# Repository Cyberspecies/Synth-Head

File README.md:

# Synth Head
To create an open source suit which can be worn by an individual and customised to their will. It also must be constructed in such a way that an average human could build it within a reasonable budget and time. The suit must be modular whilst remaining safe for the user to operate. The software must be easy to configure for any individual and has capability to modify without the need to always reflashing its firmware. The project was created according to this standard however, it has evolved over time to be more of a testing ground for sensors and other features of the like as I will continue this along with other projects I have due to compatibility.

## Overview
This project is always in the works and will be updated. Although regular updates are not possible due to me still being in uni, I will do what I can. This repo is basically a better version of the other repo and a true migration as the old one due to its structure. The reason for it being a new repo rather then just a fix is cause the title changed so the old link wouldn't have worked anyway. The current design is DX which stands for Design 10 as it is the 10th time the base shape has changed, the .3 at the end is an iterator for which version were on.

### Features
* <strong style='color: #99ccff;'>Vacuum Formed Visor</strong> allows the user to see out of a clear shell rather then the previous mesh version which caused chromatic abberation, preventing the true colours of the display from emiting through the visor properly.
* <strong style='color: #99ccff;'>Detachable Substructure</strong> which conformes to the visor ridge provides an easy to modify platform to which different displays, sensors and other modules.
* <strong style='color: #99ccff;'>Builtin Head Restraint</strong> was designed to hold in an average head with relatively high pressure, although the pressure seems like it cause pain, the addition of a foam pad mitigates this and is actually comfortable to wear.
* <strong style='color: #99ccff;'>Silent Slim Jaw Mount</strong> of around 6mm in total thickness is directly integrated to the shell.
* <strong style='color: #99ccff;'>Snoot Sensors</strong> All of the sensors and modules are attached directly into the detachable substructure and can easily be replaced and upgraded as needed, many of which includes: Boop detection, snoot holding detection & IMUs.
* <strong style='color: #99ccff;'>Ventillation</strong> is key to an alive and well user, there are 2 fans located below the tongue which negatively ventillates the user.

### In the works
* The visor edge and mating surface will be changed due to it currently resulting in an uneven edge to edge connection.
* The builtin head restraint will also be upgraded, although the system works it is not the best designed as it is currently difficult to put the pins in place.
* Electronics & other cabling will be hidden in the final release as it is not compact due to the Rushed version built for speed and prototyping rather then stability.
* ARCOS migration is still under play, the entire library is basically being rewritten slowly so it runs faster with more features. The library is currently not accessable as it is privated but it will be released with the release of the synth head 10.3.
* <strong style='color: #ffb3ff;'>Feature Inclusion:</strong> Cable management
* <strong style='color: #ffb3ff;'>Feature Inclusion:</strong> Visor Edge Alignment Upgrade
* <strong style='color: #ffb3ff;'>Feature Inclusion:</strong> Ventillation Upgrade
* <strong style='color: #ffb3ff;'>Feature Inclusion:</strong> Jaw Mount Upgrade (Attached to head restraint)
* <strong style='color: #ffb3ff;'>Feature Inclusion:</strong> Lighter Frame
* <strong style='color: #ffb3ff;'>Feature Inclusion:</strong> Custom PCB (Control Board, Power & Sensors)

### Roadmap
* <strong style='color: #99ff99;'>Milestone:</strong> [Synth Head DX](/Archives/DX/README.md)
* <strong style='color: #99ff99;'>Milestone:</strong> [Synth Head DX.1](/Archives/DX.1/README.md)
* <strong style='color: #99ff99;'>Milestone:</strong> [Synth Head DX.2 Rushed](/Archives/DX.2%20Rushed/README.md)
* <strong style='color: #99ff99;'>Milestone:</strong> [Synth Head DX.3 Rushed](/Archives/DX.3%20Rushed/README.md)
* <strong style='color: #99ff99;'>Milestone:</strong> Properly Structured Github

### Licensing
* GNU-GPL-3.0: All Software
* CC-NONCOMM: All Hardware (Circuits, CAD, etc)

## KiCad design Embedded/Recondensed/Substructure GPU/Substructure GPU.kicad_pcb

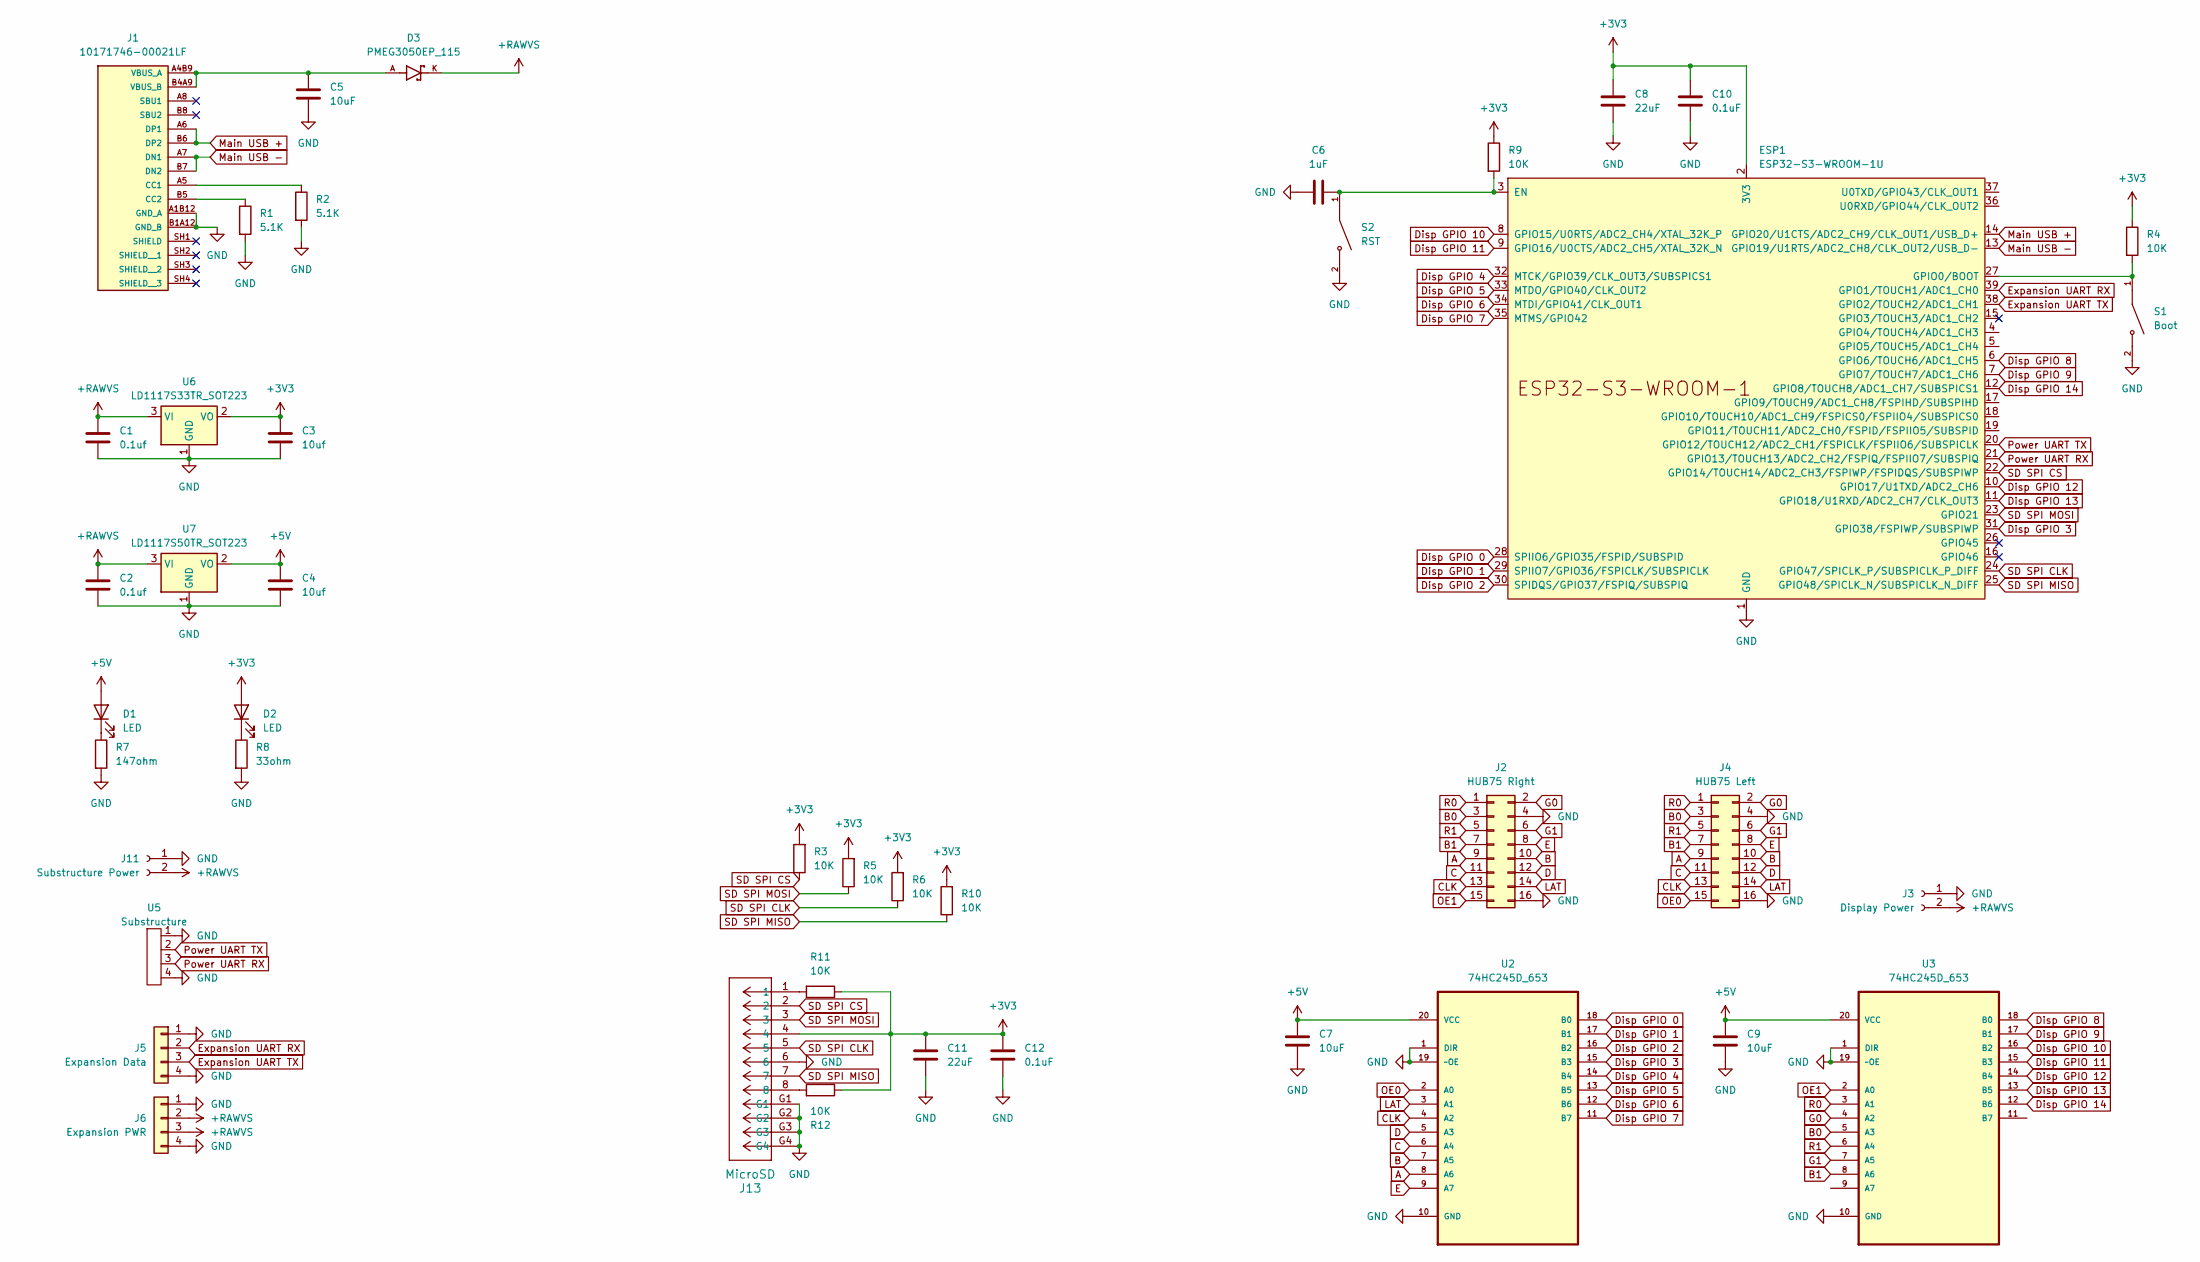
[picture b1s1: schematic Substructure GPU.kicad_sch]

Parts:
C1, C2: 0.1uf; C_0603_1608Metric_Pad1.08x0.95mm_HandSolder; LCSC C1591
C3, C4: 10uf; C_0603_1608Metric_Pad1.08x0.95mm_HandSolder; LCSC C3039698
C5: 10uF; C_0603_1608Metric; LCSC C3039698
C6: 1uF; C_0603_1608Metric_Pad1.08x0.95mm_HandSolder; LCSC C95843
C7, C9: 10uF; C_0603_1608Metric_Pad1.08x0.95mm_HandSolder; LCSC C3039698
C8, C11: 22uF; C_0603_1608Metric_Pad1.08x0.95mm_HandSolder; LCSC C84419
C10, C12: 0.1uF; C_0603_1608Metric_Pad1.08x0.95mm_HandSolder; LCSC C1591
D1, D2: LED; D_0603_1608Metric_Pad1.05x0.95mm_HandSolder; LCSC C7207730
D3: PMEG3050EP_115; DIO_PMEG3050EP_115; LCSC C50603
ESP1: ESP32-S3-WROOM-1U
J1: 10171746-00021LF; MOLEX_2171790001; PARTREV A; LCSC C3197684
J2: HUB75 Right; PinHeader_2x08_P2.54mm_Vertical; LCSC C492425
J3: Display Power; AMASS_XT30U-M_1x02_P5.0mm_Vertical
J4: HUB75 Left; PinHeader_2x08_P2.54mm_Vertical; LCSC C492425
J5: Expansion Data; PinSocket_1x04_P2.54mm_Vertical
J6: Expansion PWR; PinSocket_1x04_P2.54mm_Vertical
J11: Substructure Power; AMASS_XT30U-M_1x02_P5.0mm_Vertical
J13: MicroSD; MicroSD_473092651; LCSC C587826
R1, R2: 5.1K; R_0603_1608Metric; LCSC C328432
R3, R4, R5, R6, R9, R10, R11, R12: 10K; R_0603_1608Metric; LCSC C98220
R7: 147ohm; C_0603_1608Metric_Pad1.08x0.95mm_HandSolder; LCSC C2930065
R8: 33ohm; C_0603_1608Metric_Pad1.08x0.95mm_HandSolder; LCSC C105588
S1: Boot; SW_B3U-1000P; LCSC C231329
S2: RST; SW_B3U-1000P; LCSC C231329
U2, U3: 74HC245D_653; SOIC127P1032X265-20N; MPN 74HC245D,653; LCSC C5625
U5: Substructure; FFC-4-0.5
U6: LD1117S33TR_SOT223; SOT-223-3_TabPin2; LCSC C86781
U7: LD1117S50TR_SOT223; SOT-223-3_TabPin2; LCSC C134077

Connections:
+3V3: C3.1, C8.1, C10.1, C11.1, C12.1, D2.2 (A), ESP1.2 (3V3), J13.4, R3.2, R4.1, R5.2, R6.2, R9.1, R10.2, R11.1, R12.1, U6.2 (VO)
+5V: C4.1, C7.1, C9.1, D1.2 (A), U2.20 (VCC), U3.20 (VCC), U7.2 (VO)
+RAWVS: C1.1, C2.1, D3.K, J3.2, J6.2, J6.3, J11.2, U6.3 (VI), U7.3 (VI)
A: J2.9, J4.9, U2.8 (A6)
B: J2.10, J4.10, U2.7 (A5)
B0: J2.3, J4.3, U3.5 (A3)
B1: J2.7, J4.7, U3.8 (A6)
C: J2.11, J4.11, U2.6 (A4)
CLK: J2.13, J4.13, U2.4 (A2)
D: J2.12, J4.12, U2.5 (A3)
Disp GPIO 0: ESP1.28 (SPIIO6/GPIO35/FSPID/SUBSPID), U2.18 (B0)
Disp GPIO 1: ESP1.29 (SPIIO7/GPIO36/FSPICLK/SUBSPICLK), U2.17 (B1)
Disp GPIO 2: ESP1.30 (SPIDQS/GPIO37/FSPIQ/SUBSPIQ), U2.16 (B2)
Disp GPIO 3: ESP1.31 (GPIO38/FSPIWP/SUBSPIWP), U2.15 (B3)
Disp GPIO 4: ESP1.32 (MTCK/GPIO39/CLK_OUT3/SUBSPICS1), U2.14 (B4)
Disp GPIO 5: ESP1.33 (MTDO/GPIO40/CLK_OUT2), U2.13 (B5)
Disp GPIO 6: ESP1.34 (MTDI/GPIO41/CLK_OUT1), U2.12 (B6)
Disp GPIO 7: ESP1.35 (MTMS/GPIO42), U2.11 (B7)
Disp GPIO 8: ESP1.6 (GPIO6/TOUCH6/ADC1_CH5), U3.18 (B0)
Disp GPIO 9: ESP1.7 (GPIO7/TOUCH7/ADC1_CH6), U3.17 (B1)
Disp GPIO 10: ESP1.8 (GPIO15/U0RTS/ADC2_CH4/XTAL_32K_P), U3.16 (B2)
Disp GPIO 11: ESP1.9 (GPIO16/U0CTS/ADC2_CH5/XTAL_32K_N), U3.15 (B3)
Disp GPIO 12: ESP1.10 (GPIO17/U1TXD/ADC2_CH6), U3.14 (B4)
Disp GPIO 13: ESP1.11 (GPIO18/U1RXD/ADC2_CH7/CLK_OUT3), U3.13 (B5)
Disp GPIO 14: ESP1.12 (GPIO8/TOUCH8/ADC1_CH7/SUBSPICS1), U3.12 (B6)
E: J2.8, J4.8, U2.9 (A7)
Expansion UART RX: ESP1.39 (GPIO1/TOUCH1/ADC1_CH0), J5.2
Expansion UART TX: ESP1.38 (GPIO2/TOUCH2/ADC1_CH1), J5.3
G0: J2.2, J4.2, U3.4 (A2)
G1: J2.6, J4.6, U3.7 (A5)
GND: C1.2, C2.2, C3.2, C4.2, C5.2, C6.1, C7.2, C8.2, C9.2, C10.2, C11.2, C12.2, ESP1.1 (GND), ESP1.40 (GND), ESP1.41 (GND), J1.A1B12 (GND_A), J1.B1A12 (GND_B), J2.4, J2.16, J3.1, J4.4, J4.16, J5.1, J5.4, J6.1, J6.4, J11.1, J13.6, J13.G1, J13.G2, J13.G3, J13.G4, R1.2, R2.2, R7.2, R8.2, S1.2, S2.2, U2.1 (DIR), U2.10 (GND), U2.19 (~OE), U3.1 (DIR), U3.10 (GND), U3.19 (~OE), U5.1, U5.4, U6.1 (GND), U7.1 (GND)
LAT: J2.14, J4.14, U2.3 (A1)
Main USB +: ESP1.14 (GPIO20/U1CTS/ADC2_CH9/CLK_OUT1/USB_D+), J1.A6 (DP1), J1.B6 (DP2)
Main USB -: ESP1.13 (GPIO19/U1RTS/ADC2_CH8/CLK_OUT2/USB_D-), J1.A7 (DN1), J1.B7 (DN2)
unnamed: D1.1 (K), R7.1
unnamed: D2.1 (K), R8.1
unnamed: C6.2, ESP1.3 (EN), R9.2, S2.1
unnamed: ESP1.27 (GPIO0/BOOT), R4.2, S1.1
unnamed: J1.A5 (CC1), R2.1
unnamed: J1.B5 (CC2), R1.1
unnamed: C5.1, D3.A, J1.A4B9 (VBUS_A), J1.B4A9 (VBUS_B)
unnamed: J13.1, R11.2
unnamed: J13.8, R12.2
OE0: J4.15, U2.2 (A0)
OE1: J2.15, U3.2 (A0)
Power UART RX: ESP1.21 (GPIO13/TOUCH13/ADC2_CH2/FSPIQ/FSPIIO7/S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), U5.3
Power UART TX: ESP1.20 (GPIO12/TOUCH12/ADC2_CH1/FSPICLK/FSPIIO6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), U5.2
R0: J2.1, J4.1, U3.3 (A1)
R1: J2.5, J4.5, U3.6 (A4)
SD SPI CLK: ESP1.24 (GPIO47/SPICLK_P/SUBSPICLK_P_DIFF), J13.5, R6.1
SD SPI CS: ESP1.22 (GPIO14/TOUCH14/ADC2_CH3/FSPIWP/FSPIDQS/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), J13.2, R3.1
SD SPI MISO: ESP1.25 (GPIO48/SPICLK_N/SUBSPICLK_N_DIFF), J13.7, R10.1
SD SPI MOSI: ESP1.23 (GPIO21), J13.3, R5.1

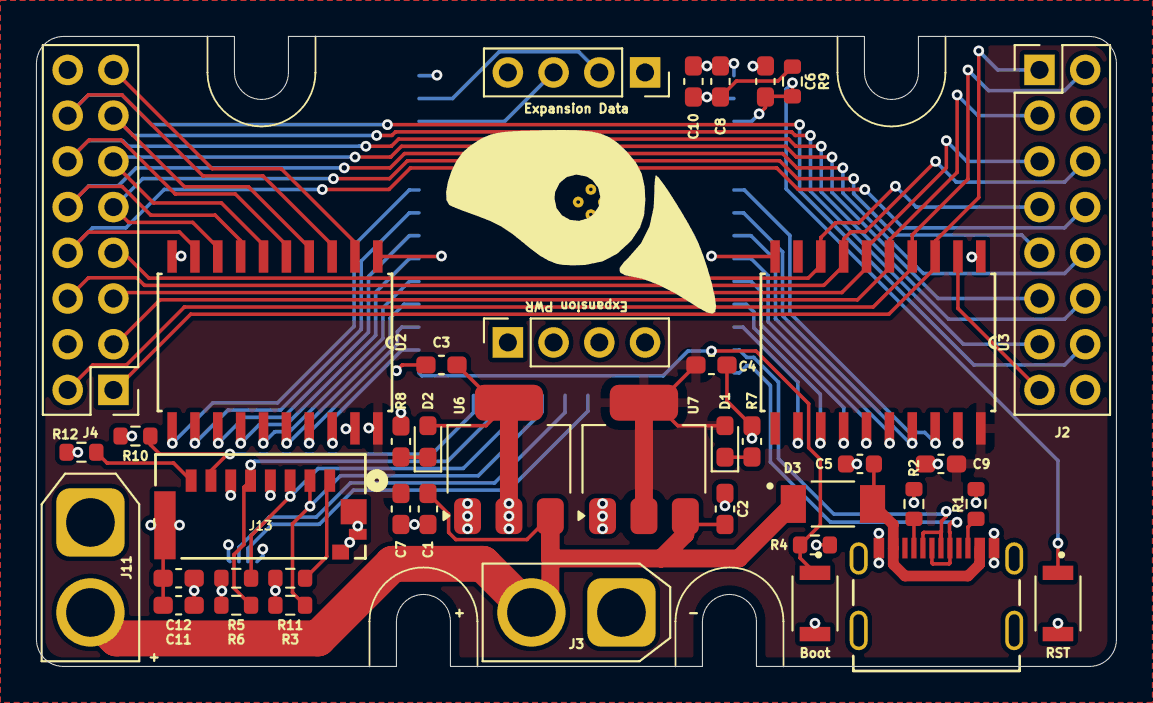
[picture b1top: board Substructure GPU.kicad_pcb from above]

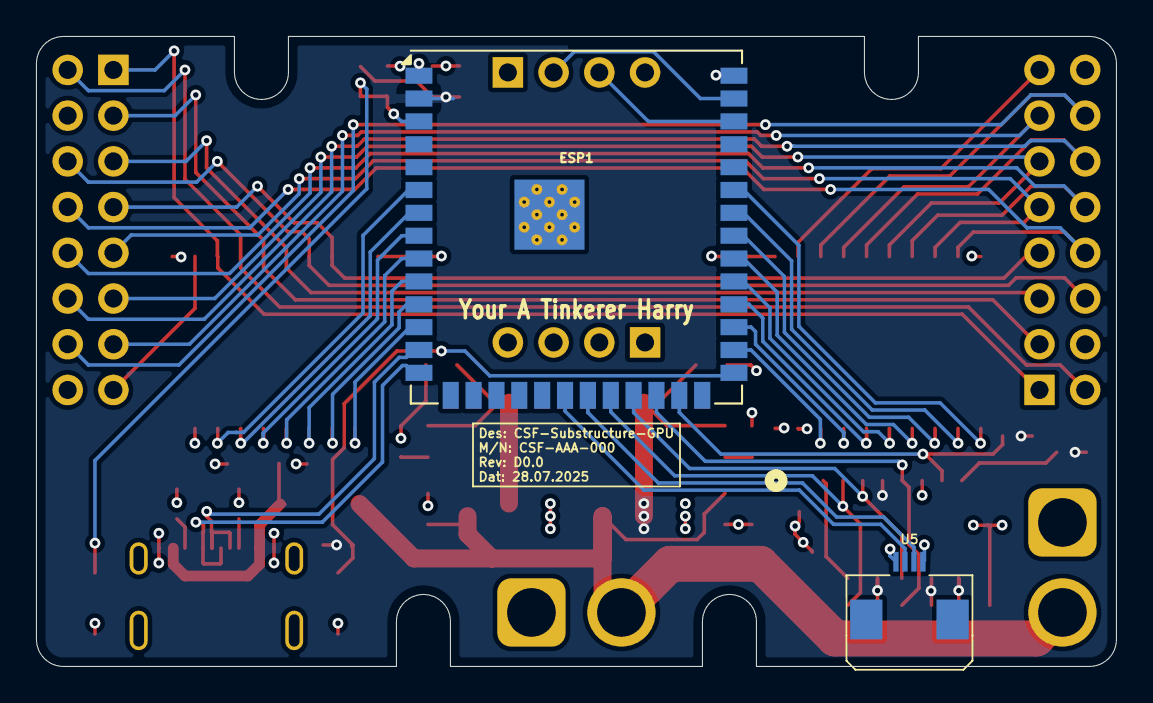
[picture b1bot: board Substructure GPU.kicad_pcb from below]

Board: 4 copper layers, 60.0 x 35.0 mm, 43 parts (2 on the bottom side), 53 nets.

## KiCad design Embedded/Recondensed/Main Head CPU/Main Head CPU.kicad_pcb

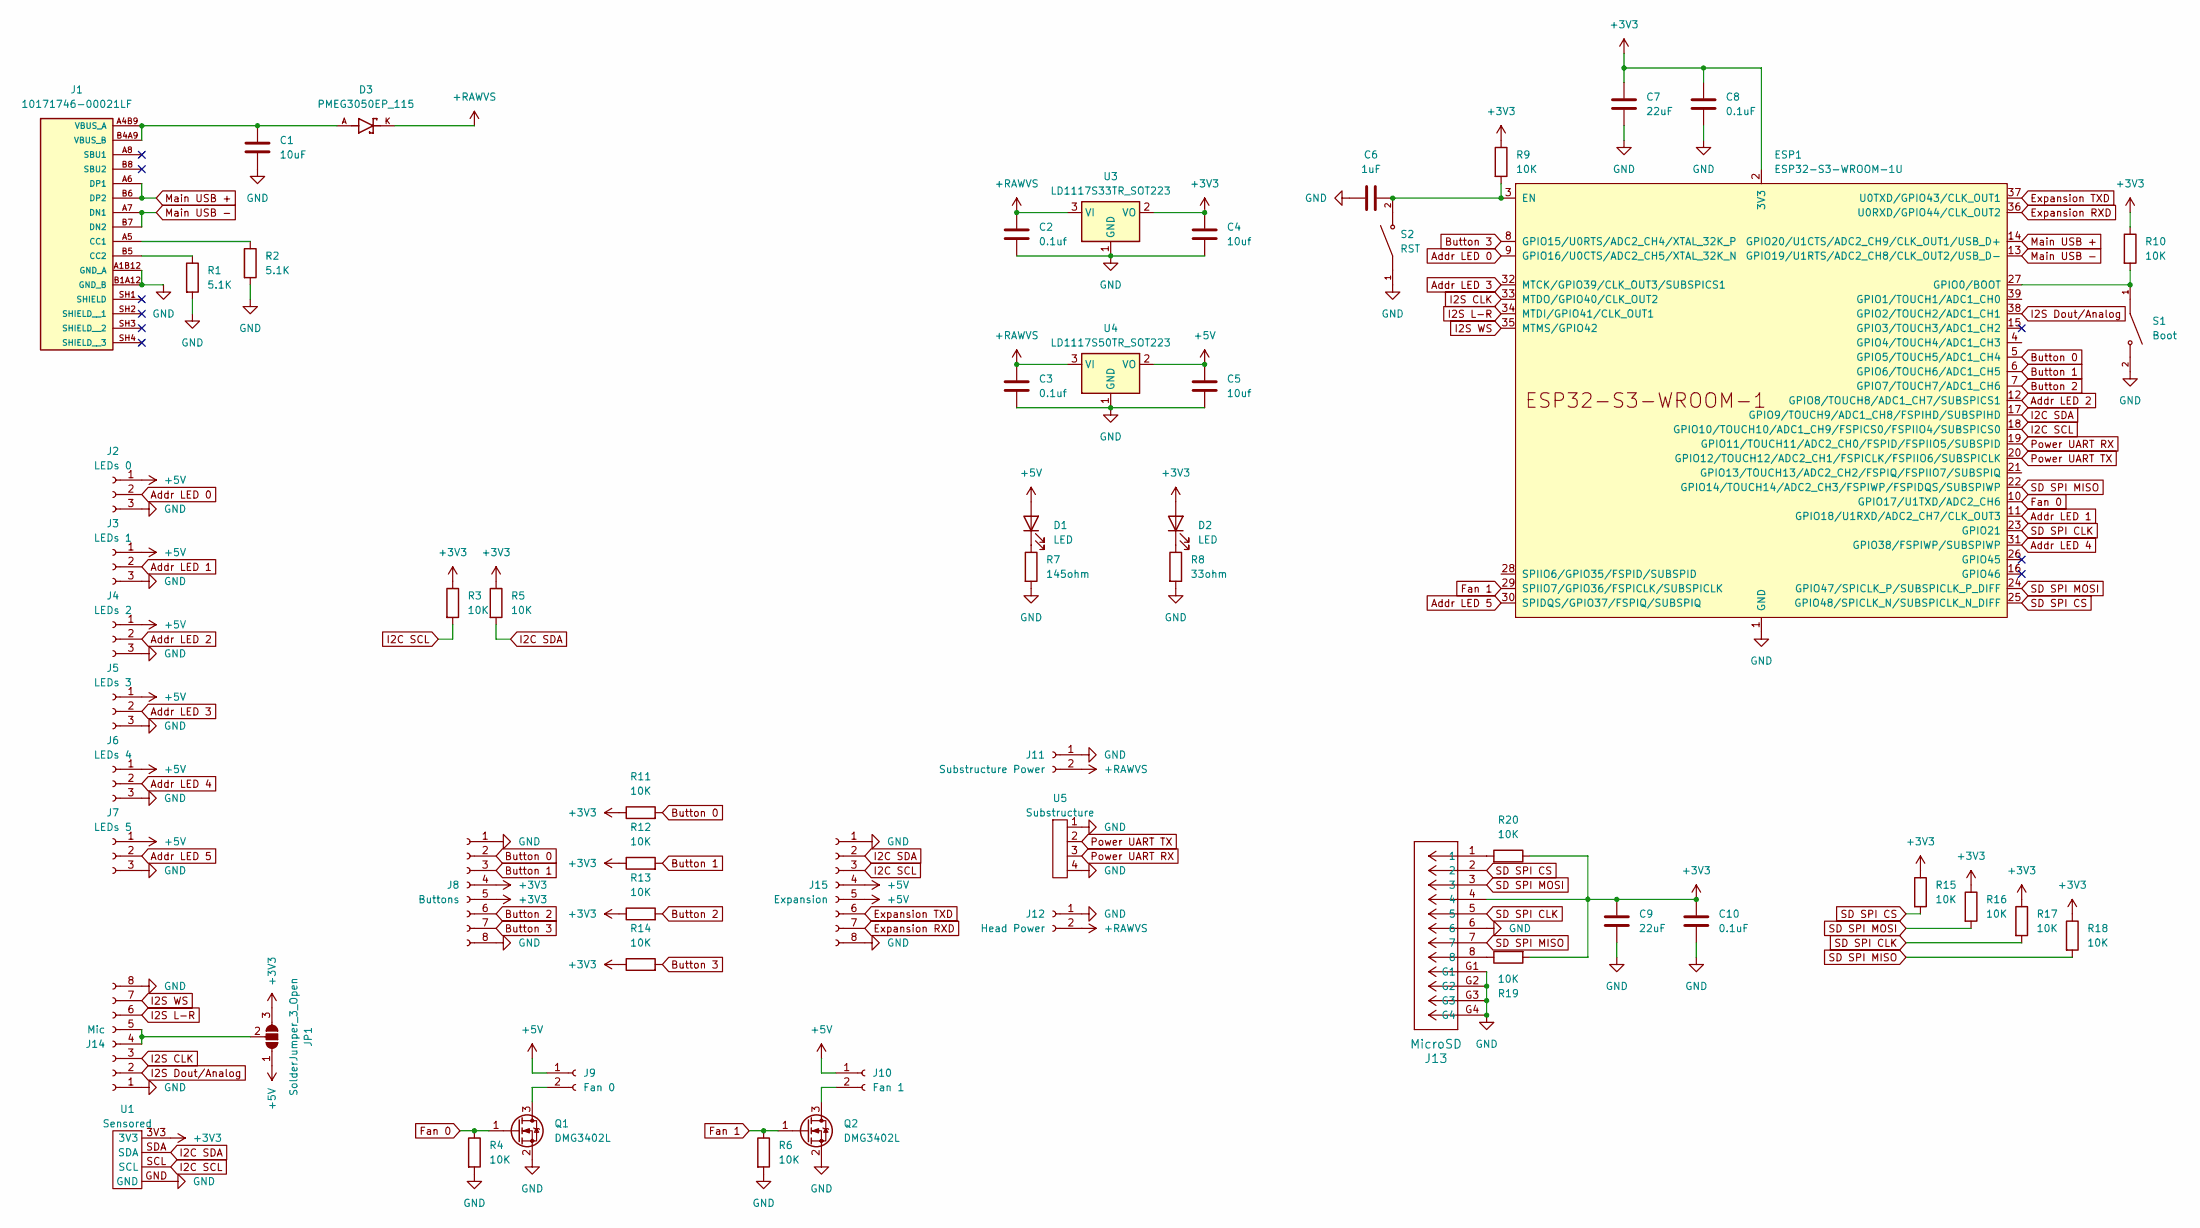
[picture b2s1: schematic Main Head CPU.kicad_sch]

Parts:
C1: 10uF; C_0603_1608Metric; LCSC C3039698
C2, C3: 0.1uf; C_0603_1608Metric_Pad1.08x0.95mm_HandSolder; LCSC C1591
C4, C5: 10uf; C_0603_1608Metric_Pad1.08x0.95mm_HandSolder; LCSC C3039698
C6: 1uF; C_0603_1608Metric_Pad1.08x0.95mm_HandSolder; LCSC C95843
C7, C9: 22uF; C_0603_1608Metric_Pad1.08x0.95mm_HandSolder; LCSC C84419
C8, C10: 0.1uF; C_0603_1608Metric_Pad1.08x0.95mm_HandSolder; LCSC C1591
D1, D2: LED; D_0603_1608Metric_Pad1.05x0.95mm_HandSolder; LCSC C7207730
D3: PMEG3050EP_115; DIO_PMEG3050EP_115; LCSC C50603
ESP1: ESP32-S3-WROOM-1U
J1: 10171746-00021LF; MOLEX_2171790001; PARTREV A; LCSC C3197684
J2: LEDs 0; JST_GH_SM03B-GHS-TB_1x03-1MP_P1.25mm_Horizontal; LCSC C514175
J3: LEDs 1; JST_GH_SM03B-GHS-TB_1x03-1MP_P1.25mm_Horizontal; LCSC C514175
J4: LEDs 2; JST_GH_SM03B-GHS-TB_1x03-1MP_P1.25mm_Horizontal; LCSC C514175
J5: LEDs 3; JST_GH_SM03B-GHS-TB_1x03-1MP_P1.25mm_Horizontal; LCSC C514175
J6: LEDs 4; JST_GH_SM03B-GHS-TB_1x03-1MP_P1.25mm_Horizontal; LCSC C514175
J7: LEDs 5; JST_GH_SM03B-GHS-TB_1x03-1MP_P1.25mm_Horizontal; LCSC C514175
J8: Buttons; JST_GH_SM08B-GHS-TB_1x08-1MP_P1.25mm_Horizontal; LCSC C265111
J9: Fan 0; JST_GH_SM02B-GHS-TB_1x02-1MP_P1.25mm_Horizontal; LCSC C189893
J10: Fan 1; JST_GH_SM02B-GHS-TB_1x02-1MP_P1.25mm_Horizontal; LCSC C189893
J11: Substructure Power; AMASS_XT30PW-M_1x02_P2.50mm_Horizontal
J12: Head Power; AMASS_XT30PW-M_1x02_P2.50mm_Horizontal
J13: MicroSD; MicroSD_473092651; LCSC C587826
J14: Mic; JST_GH_SM08B-GHS-TB_1x08-1MP_P1.25mm_Horizontal; LCSC C265111
J15: Expansion; JST_GH_SM08B-GHS-TB_1x08-1MP_P1.25mm_Horizontal; LCSC C265111
JP1: SolderJumper_3_Open; SolderJumper-3_P1.3mm_Open_RoundedPad1.0x1.5mm
Q1, Q2: DMG3402L; SOT-23; LCSC C96614
R1, R2: 5.1K; R_0603_1608Metric; LCSC C328432
R3, R4, R5, R6, R11, R12, R13, R14, R15, R16, R17, R18, R19, R20: 10K; R_0603_1608Metric_Pad0.98x0.95mm_HandSolder; LCSC C98220
R7: 145ohm; C_0603_1608Metric_Pad1.08x0.95mm_HandSolder; LCSC C2930065
R8: 33ohm; C_0603_1608Metric_Pad1.08x0.95mm_HandSolder; LCSC C108661
R9, R10: 10K; R_0603_1608Metric; LCSC C98220
S1: Boot; SW_B3U-1000P; LCSC C231329
S2: RST; SW_B3U-1000P; LCSC C231329
U1: Sensored
U3: LD1117S33TR_SOT223; SOT-223-3_TabPin2; LCSC C86781
U4: LD1117S50TR_SOT223; SOT-223-3_TabPin2; LCSC C134077
U5: Substructure; FFC-4-0.5

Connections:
+3V3: C4.1, C7.1, C8.1, C9.1, C10.1, D2.2 (A), ESP1.2 (3V3), J8.4, J8.5, J13.4, JP1.3 (B), R3.1, R5.1, R9.1, R10.1, R11.1, R12.1, R13.1, R14.1, R15.1, R16.1, R17.1, R18.1, R19.2, R20.1, U1.3V3, U3.2 (VO)
+5V: C5.1, D1.2 (A), J2.1, J3.1, J4.1, J5.1, J6.1, J7.1, J9.1, J10.1, J15.4, J15.5, JP1.1 (A), U4.2 (VO)
+RAWVS: C2.1, C3.1, D3.K, J11.2, J12.2, U3.3 (VI), U4.3 (VI)
Addr LED 0: ESP1.9 (GPIO16/U0CTS/ADC2_CH5/XTAL_32K_N), J2.2
Addr LED 1: ESP1.11 (GPIO18/U1RXD/ADC2_CH7/CLK_OUT3), J3.2
Addr LED 2: ESP1.12 (GPIO8/TOUCH8/ADC1_CH7/SUBSPICS1), J4.2
Addr LED 3: ESP1.32 (MTCK/GPIO39/CLK_OUT3/SUBSPICS1), J5.2
Addr LED 4: ESP1.31 (GPIO38/FSPIWP/SUBSPIWP), J6.2
Addr LED 5: ESP1.30 (SPIDQS/GPIO37/FSPIQ/SUBSPIQ), J7.2
Button 0: ESP1.5 (GPIO5/TOUCH5/ADC1_CH4), J8.2, R11.2
Button 1: ESP1.6 (GPIO6/TOUCH6/ADC1_CH5), J8.3, R12.2
Button 2: ESP1.7 (GPIO7/TOUCH7/ADC1_CH6), J8.6, R13.2
Button 3: ESP1.8 (GPIO15/U0RTS/ADC2_CH4/XTAL_32K_P), J8.7, R14.2
Expansion RXD: ESP1.36 (U0RXD/GPIO44/CLK_OUT2), J15.7
Expansion TXD: ESP1.37 (U0TXD/GPIO43/CLK_OUT1), J15.6
Fan 0: ESP1.10 (GPIO17/U1TXD/ADC2_CH6), Q1.1 (G), R4.1
Fan 1: ESP1.29 (SPIIO7/GPIO36/FSPICLK/SUBSPICLK), Q2.1 (G), R6.1
GND: C1.2, C2.2, C3.2, C4.2, C5.2, C6.1, C7.2, C8.2, C9.2, C10.2, ESP1.1 (GND), ESP1.40 (GND), ESP1.41 (GND), J1.A1B12 (GND_A), J1.B1A12 (GND_B), J2.3, J3.3, J4.3, J5.3, J6.3, J7.3, J8.1, J8.8, J11.1, J12.1, J13.6, J13.G1, J13.G2, J13.G3, J13.G4, J14.1, J14.8, J15.1, J15.8, Q1.2 (S), Q2.2 (S), R1.2, R2.2, R4.2, R6.2, R7.2, R8.2, S1.2, S2.1, U1.GND, U3.1 (GND), U4.1 (GND), U5.1, U5.4
I2C SCL: ESP1.18 (GPIO10/TOUCH10/ADC1_CH9/FSPICS0/FSPIIO4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), J15.3, R3.2, U1.SCL
I2C SDA: ESP1.17 (GPIO9/TOUCH9/ADC1_CH8/FSPIHD/SUBSPIHD), J15.2, R5.2, U1.SDA
I2S CLK: ESP1.33 (MTDO/GPIO40/CLK_OUT2), J14.3
I2S Dout/Analog: ESP1.38 (GPIO2/TOUCH2/ADC1_CH1), J14.2
I2S L-R: ESP1.34 (MTDI/GPIO41/CLK_OUT1), J14.6
I2S WS: ESP1.35 (MTMS/GPIO42), J14.7
Main USB +: ESP1.14 (GPIO20/U1CTS/ADC2_CH9/CLK_OUT1/USB_D+), J1.A6 (DP1), J1.B6 (DP2)
Main USB -: ESP1.13 (GPIO19/U1RTS/ADC2_CH8/CLK_OUT2/USB_D-), J1.A7 (DN1), J1.B7 (DN2)
unnamed: D1.1 (K), R7.1
unnamed: D2.1 (K), R8.1
unnamed: C6.2, ESP1.3 (EN), R9.2, S2.2
unnamed: ESP1.27 (GPIO0/BOOT), R10.2, S1.1
unnamed: J1.A5 (CC1), R2.1
unnamed: J1.B5 (CC2), R1.1
unnamed: C1.1, D3.A, J1.A4B9 (VBUS_A), J1.B4A9 (VBUS_B)
unnamed: J9.2, Q1.3 (D)
unnamed: J10.2, Q2.3 (D)
unnamed: J13.1, R20.2
unnamed: J13.8, R19.1
unnamed: J14.4, J14.5, JP1.2 (C)
Power UART RX: ESP1.19 (GPIO11/TOUCH11/ADC2_CH0/FSPID/FSPIIO5/S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), U5.3
Power UART TX: ESP1.20 (GPIO12/TOUCH12/ADC2_CH1/FSPICLK/FSPIIO6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), U5.2
SD SPI CLK: ESP1.23 (GPIO21), J13.5, R17.2
SD SPI CS: ESP1.25 (GPIO48/SPICLK_N/SUBSPICLK_N_DIFF), J13.2, R15.2
SD SPI MISO: ESP1.22 (GPIO14/TOUCH14/ADC2_CH3/FSPIWP/FSPIDQS/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), J13.7, R18.2
SD SPI MOSI: ESP1.24 (GPIO47/SPICLK_P/SUBSPICLK_P_DIFF), J13.3, R16.2

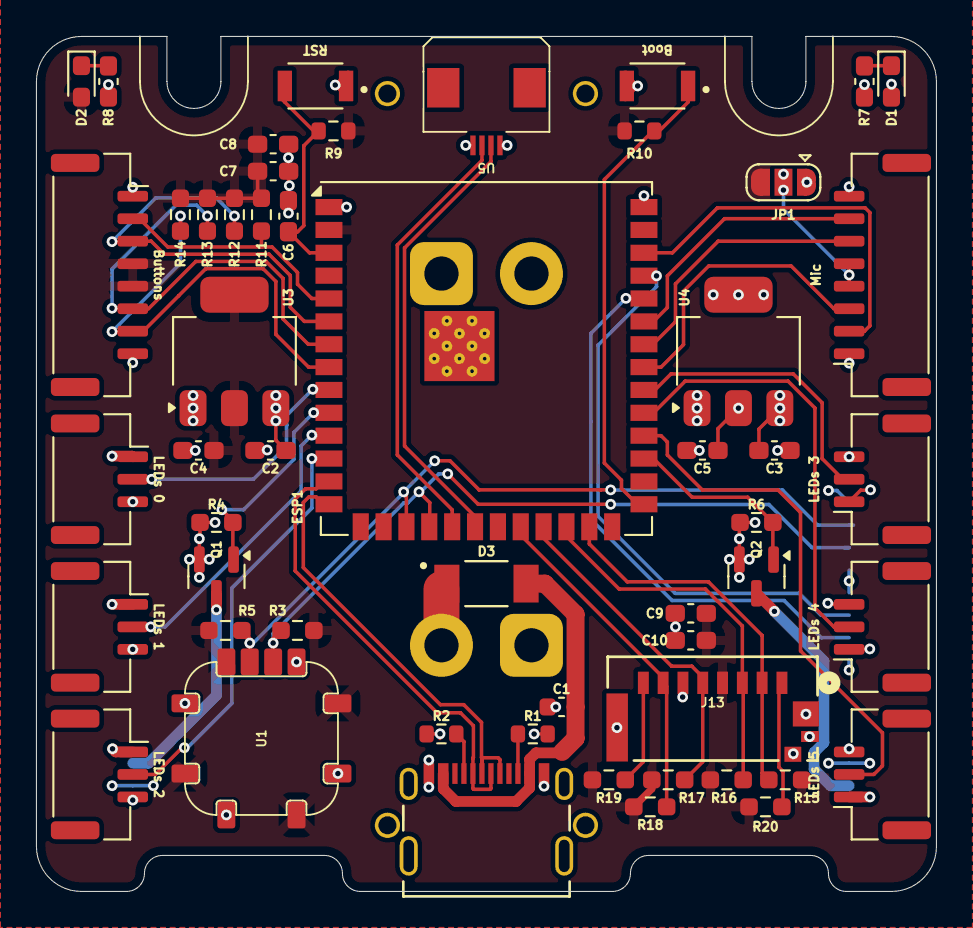
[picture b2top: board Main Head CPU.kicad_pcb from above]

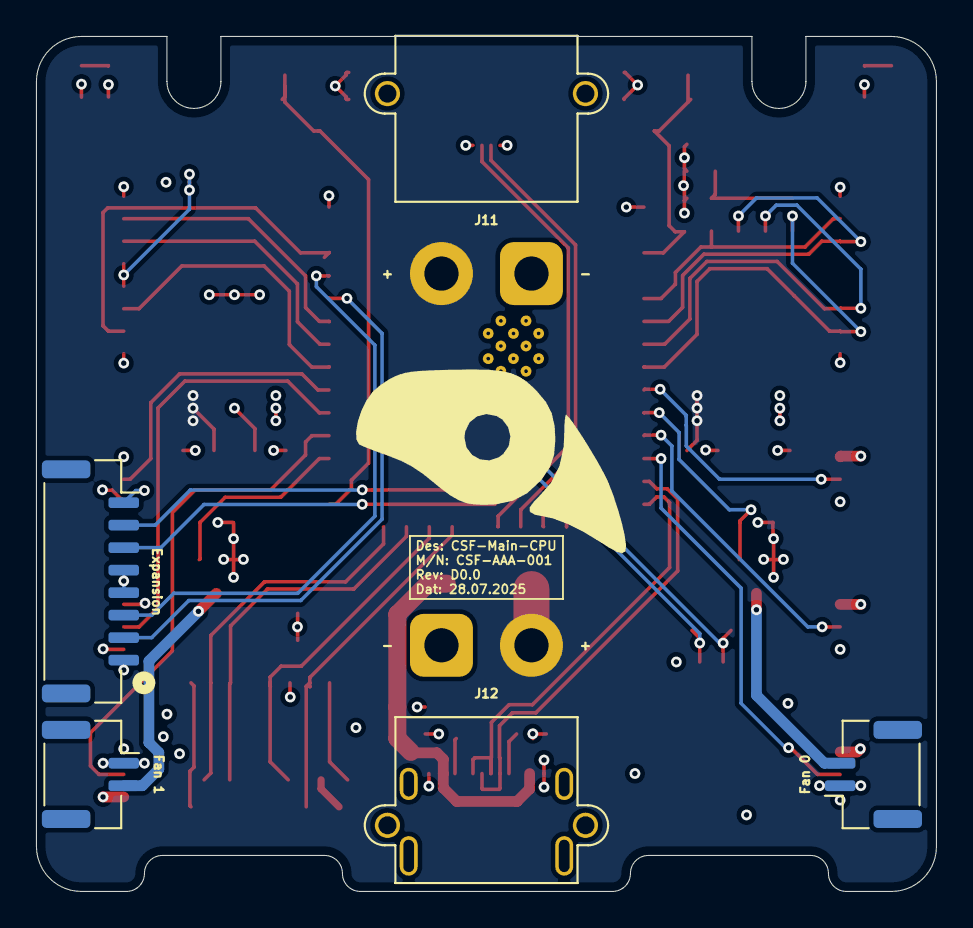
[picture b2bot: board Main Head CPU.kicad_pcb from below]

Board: 4 copper layers, 50.0 x 47.5 mm, 58 parts (5 on the bottom side), 44 nets.

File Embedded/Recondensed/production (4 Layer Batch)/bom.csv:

Designator,Footprint,Quantity,Value,LCSC Part #
"C1_2, C3, C4_2, C4, C5_2, C5, C7, C9",0603,8,10uF,C3039698
"C1, C10_2, C10, C12, C2_2, C2, C3_2, C8_2",0603,8,0.1uf,C1591
"C11, C7_2, C8, C9_2",0603,4,22uF,C84419
"C6_2, C6",0603,2,1uF,C95843
"D1_2, D1, D2_2, D2",0603,4,LED,C7207730
"D3_2, D3",DIO_PMEG3050EP_115,2,PMEG3050EP_115,C50603
"J1_2, J1",MOLEX_2171790001,2,10171746-00021LF,C3197684
J10,JST_GH_SM02B-GHS-TB_1x02-1MP_P1.25mm_Horizontal,1,Fan 1,C189893
"J13_2, J13",MicroSD_473092651,2,MicroSD,C587826
J14,JST_GH_SM08B-GHS-TB_1x08-1MP_P1.25mm_Horizontal,1,Mic,C265111
J15,JST_GH_SM08B-GHS-TB_1x08-1MP_P1.25mm_Horizontal,1,Expansion,C265111
J2_2,JST_GH_SM03B-GHS-TB_1x03-1MP_P1.25mm_Horizontal,1,LEDs 0,C514175
J2,PinHeader_2x08_P2.54mm_Vertical,1,HUB75 Right,C492425
J3_2,JST_GH_SM03B-GHS-TB_1x03-1MP_P1.25mm_Horizontal,1,LEDs 1,C514175
J4_2,JST_GH_SM03B-GHS-TB_1x03-1MP_P1.25mm_Horizontal,1,LEDs 2,C514175
J4,PinHeader_2x08_P2.54mm_Vertical,1,HUB75 Left,C492425
J5_2,JST_GH_SM03B-GHS-TB_1x03-1MP_P1.25mm_Horizontal,1,LEDs 3,C514175
J6_2,JST_GH_SM03B-GHS-TB_1x03-1MP_P1.25mm_Horizontal,1,LEDs 4,C514175
J7,JST_GH_SM03B-GHS-TB_1x03-1MP_P1.25mm_Horizontal,1,LEDs 5,C514175
J8,JST_GH_SM08B-GHS-TB_1x08-1MP_P1.25mm_Horizontal,1,Buttons,C265111
J9,JST_GH_SM02B-GHS-TB_1x02-1MP_P1.25mm_Horizontal,1,Fan 0,C189893
"Q1, Q2",SOT-23,2,DMG3402L,C96614
"R1_2, R1, R2_2, R2",0603,4,5.1K,C328432
"R10, R11, R12, R13, R14, R3, R4_2, R4, R5, R6, R9_2, R9",0603,12,10K,C98220
R7_2,0603,1,145ohm,C2930065
R7,0603,1,147ohm,C2930065
R8_2,0603,1,33ohm,C108661
R8,0603,1,33ohm,C105588
S1_2,SW_B3U-1000P,1,Boot,C231329 
S1,SW_B3U-1000P,1,Boot,C231329
S2_2,SW_B3U-1000P,1,RST,C231329 
S2,SW_B3U-1000P,1,RST,C231329
U1,Sensored,1,Sensored,
"U2, U3",SOIC127P1032X265-20N,2,74HC245D_653,C5625
"U3_2, U6",SOT-223-3_TabPin2,2,LD1117S33TR_SOT223,C86781
"U4, U7",SOT-223-3_TabPin2,2,LD1117S50TR_SOT223,C134077

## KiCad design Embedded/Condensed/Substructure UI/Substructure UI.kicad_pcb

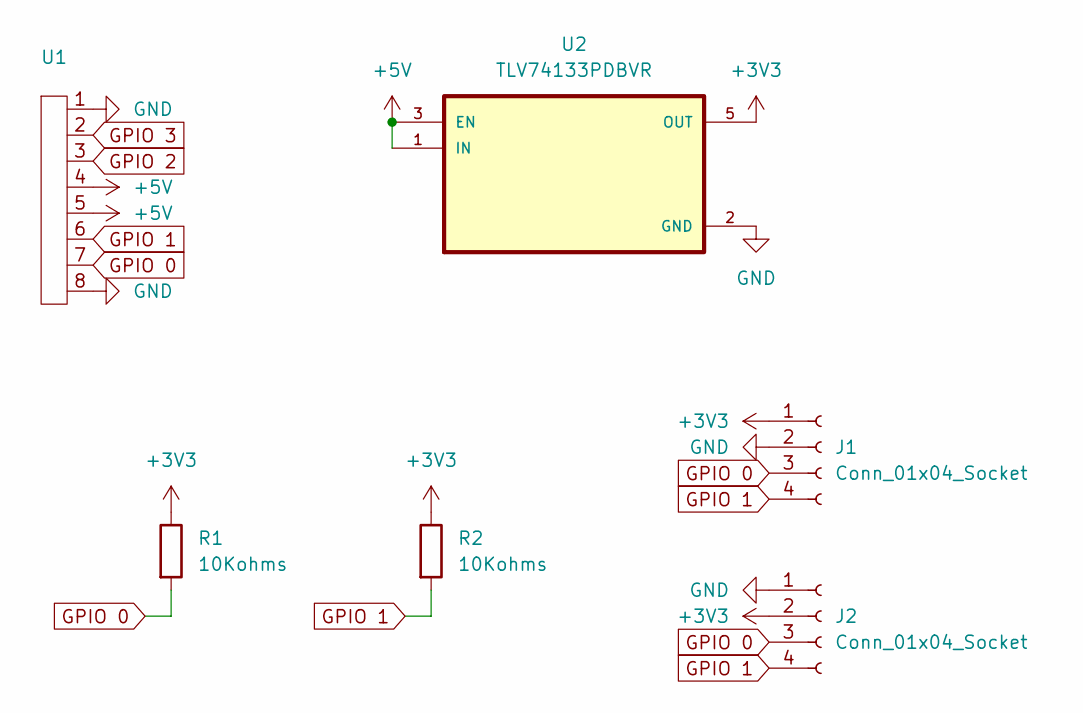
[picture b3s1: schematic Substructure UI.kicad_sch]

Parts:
J1, J2: Conn_01x04_Socket; PinHeader_1x04_P2.54mm_Vertical
R1, R2: 10Kohms; R_0603_1608Metric_Pad0.98x0.95mm_HandSolder
U1: FFC 0.8mm 8P
U2: TLV74133PDBVR; SOT95P280X145-5N

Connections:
+3V3: J1.1, J2.2, R1.1, R2.1, U2.5 (OUT)
+5V: U1.4, U1.5, U2.1 (IN), U2.3 (EN)
GND: J1.2, J2.1, U1.1, U1.8, U2.2 (GND)
GPIO 0: J1.3, J2.3, R1.2, U1.7
GPIO 1: J1.4, J2.4, R2.2, U1.6
GPIO 2: U1.3
GPIO 3: U1.2

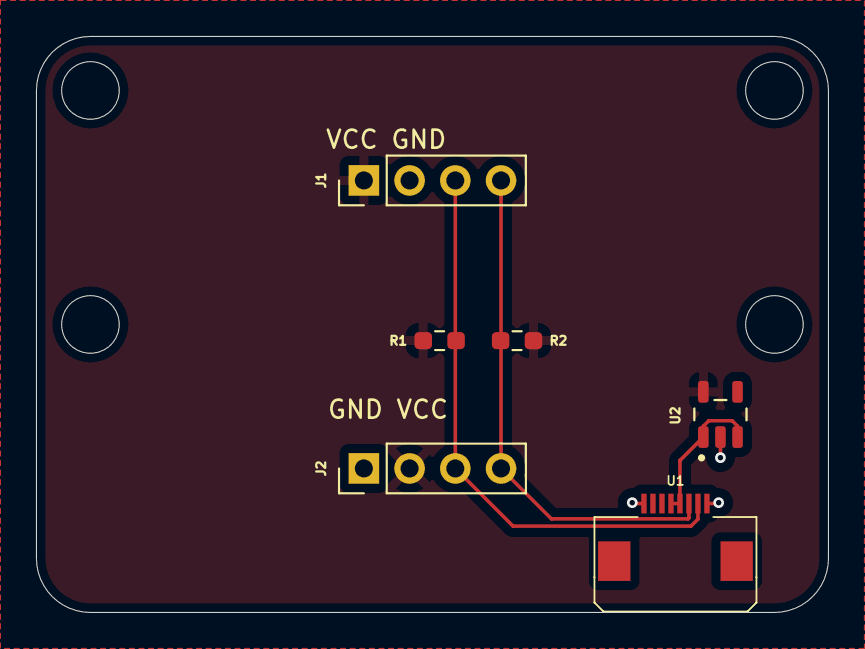
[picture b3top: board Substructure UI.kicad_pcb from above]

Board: 2 copper layers, 44.0 x 32.0 mm, 6 parts (0 on the bottom side), 5 nets.

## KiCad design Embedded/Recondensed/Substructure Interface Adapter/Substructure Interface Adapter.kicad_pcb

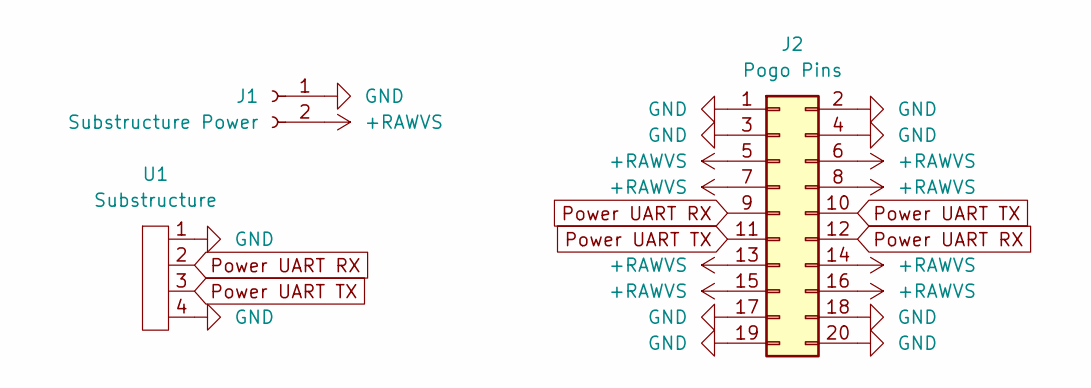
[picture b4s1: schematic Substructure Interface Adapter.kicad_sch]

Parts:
J1: Substructure Power; AMASS_XT30PW-M_1x02_P2.50mm_Horizontal
J2: Pogo Pins; PinHeader_2x10_P2.00mm_Vertical
U1: Substructure; FFC-4-0.5

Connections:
+RAWVS: J1.2, J2.5, J2.6, J2.7, J2.8, J2.13, J2.14, J2.15, J2.16
GND: J1.1, J2.1, J2.2, J2.3, J2.4, J2.17, J2.18, J2.19, J2.20, U1.1, U1.4
Power UART RX: J2.9, J2.12, U1.2
Power UART TX: J2.10, J2.11, U1.3

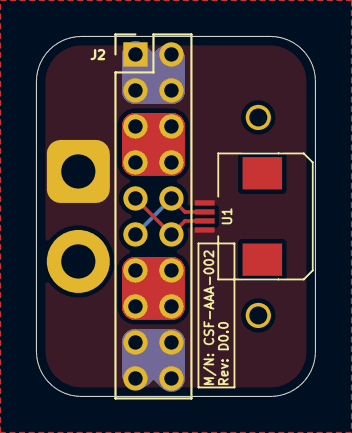
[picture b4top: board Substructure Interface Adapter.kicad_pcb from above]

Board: 2 copper layers, 15.5 x 20.0 mm, 3 parts (1 on the bottom side), 4 nets.
